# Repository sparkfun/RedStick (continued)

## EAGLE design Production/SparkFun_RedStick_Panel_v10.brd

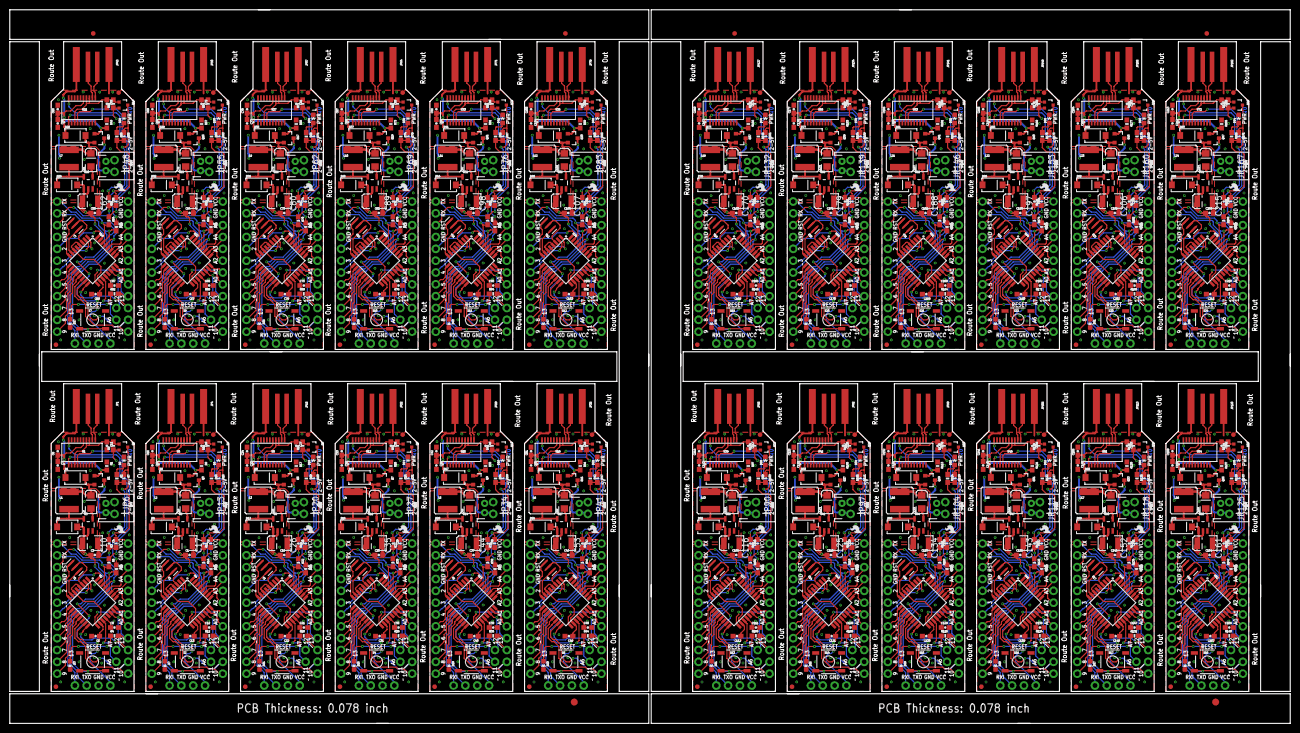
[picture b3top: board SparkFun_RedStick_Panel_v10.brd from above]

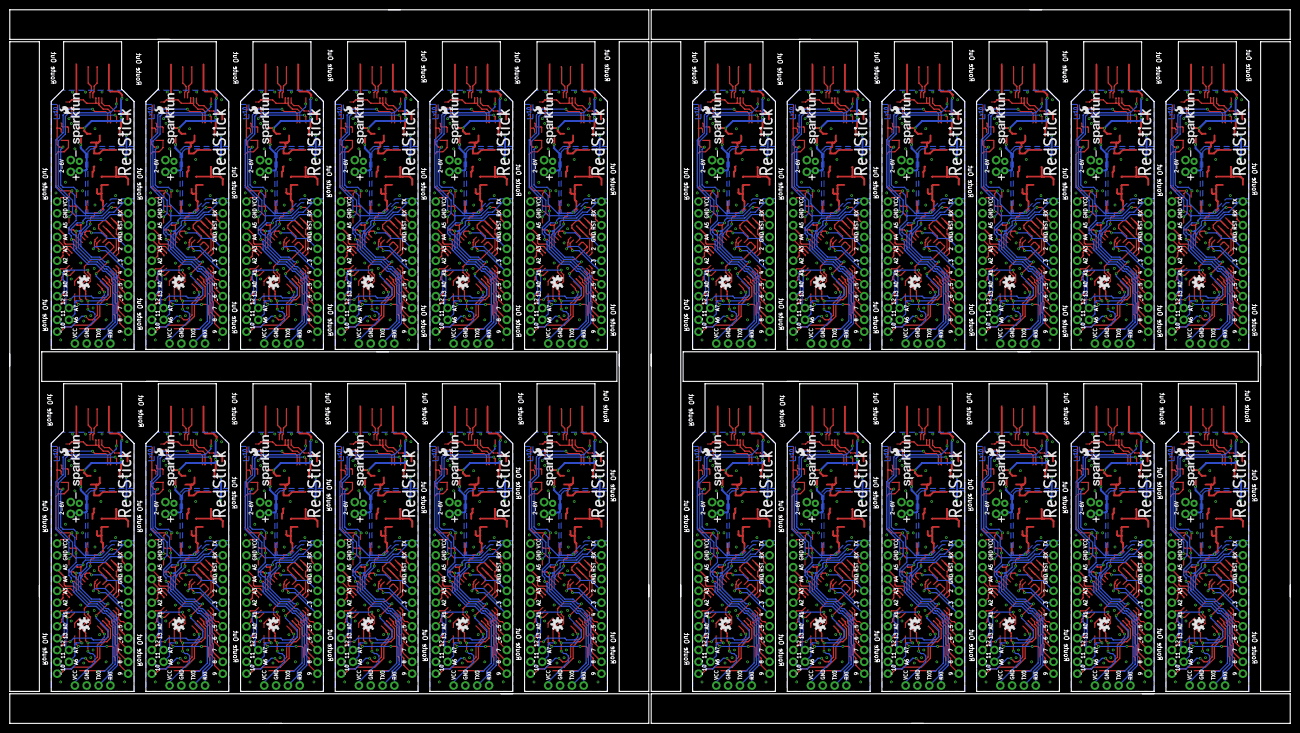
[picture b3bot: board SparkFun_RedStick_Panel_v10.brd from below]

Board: 2 copper layers, 274.8 x 153.2 mm, 990 parts (48 on the bottom side), 984 nets.

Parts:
C1, C2, C3, C4, C5, C6, C7, C8, C11, C12, C13, C14, C15, C18, C19, C20, C21, C22, C23, C24, C27, C28, C29, C30, C31, C32, C33, C36, C37, C38, C39, C40, C41, C42, C45, C46, C47, C48, C49, C50, C51, C54, C55, C56, C57, C58, C59, C60, C63, C64, C65, C66, C67, C68, C69, C72, C73, C74, C75, C76, C77, C78, C81, C82, C83, C84, C85, C86, C87, C90, C91, C92, C93, C94, C95, C96, C99, C100, C101, C102, C103, C104, C105, C108, C109, C110, C111, C112, C113, C114, C117, C118, C119, C120, C121, C122, C123, C126, C127, C128, C129, C130, C131, C132, C135, C136, C137, C138, C139, C140, C141, C144, C145, C146, C147, C148, C149, C150, C153, C154, C155, C156, C157, C158, C159, C162, C163, C164, C165, C166, C167, C168, C171, C172, C173, C174, C175, C176, C177, C180, C181, C182, C183, C184, C185, C186, C189, C190, C191, C192, C193, C194, C195, C198, C199, C200, C201, C202, C203, C204, C207, C208, C209, C210, C211, C212, C213, C216: 0.1uF; 0603-CAP
C9, C16, C25, C34, C43, C52, C61, C70, C79, C88, C97, C106, C115, C124, C133, C142, C151, C160, C169, C178, C187, C196, C205, C214: 10uF; EIA3216
C10, C17, C26, C35, C44, C53, C62, C71, C80, C89, C98, C107, C116, C125, C134, C143, C152, C161, C170, C179, C188, C197, C206, C215: 68uF; EIA3528
D1, D4, D5, D8, D9, D12, D13, D16, D17, D20, D21, D24, D25, D28, D29, D32, D33, D36, D37, D40, D41, D44, D45, D48, D49, D52, D53, D56, D57, D60, D61, D64, D65, D68, D69, D72, D73, D76, D77, D80, D81, D84, D85, D88, D89, D92, D93, D96: MBRA140; SMA-DIODE
D2, D6, D10, D14, D18, D22, D26, D30, D34, D38, D42, D46, D50, D54, D58, D62, D66, D70, D74, D78, D82, D86, D90, D94: RED; LED-0603
D3, D7, D11, D15, D19, D23, D27, D31, D35, D39, D43, D47, D51, D55, D59, D63, D67, D71, D75, D79, D83, D87, D91, D95: GREEN; LED-0603
E$1, E$4: FIDUCIAL-1.5X3
E$2, E$3, E$5, E$6: FIDUCIAL-1X2
FID1, FID2, FID3, FID4, FID5, FID6, FID7, FID8, FID9, FID10, FID11, FID12, FID13, FID14, FID15, FID16, FID17, FID18, FID19, FID20, FID21, FID22, FID23, FID24, FID25, FID26, FID27, FID28, FID29, FID30, FID31, FID32, FID33, FID34, FID35, FID36, FID37, FID38, FID39, FID40, FID41, FID42, FID43, FID44, FID45, FID46, FID47, FID48: FIDUCIAL1X2; FIDUCIAL-1X2
JP1, JP4, JP15, JP22, JP29, JP36, JP43, JP50, JP57, JP64, JP71, JP78, JP85, JP92, JP99, JP106, JP113, JP120, JP127, JP134, JP141, JP148, JP155, JP162: USBPCB_NOPASTE; USB-A-PCB-NOPASTE
JP2, JP3, JP10, JP11, JP17, JP18, JP24, JP25, JP31, JP32, JP38, JP39, JP45, JP46, JP52, JP53, JP59, JP60, JP66, JP67, JP73, JP74, JP80, JP81, JP87, JP88, JP94, JP95, JP101, JP102, JP108, JP109, JP115, JP116, JP122, JP123, JP129, JP130, JP136, JP137, JP143, JP144, JP150, JP151, JP157, JP158, JP164, JP165: DNP; 1X12_NO_SILK
JP5, JP6, JP9, JP13, JP16, JP20, JP23, JP27, JP30, JP34, JP37, JP41, JP44, JP48, JP51, JP55, JP58, JP62, JP65, JP69, JP72, JP76, JP79, JP83, JP86, JP90, JP93, JP97, JP100, JP104, JP107, JP111, JP114, JP118, JP121, JP125, JP128, JP132, JP135, JP139, JP142, JP146, JP149, JP153, JP156, JP160, JP163, JP167: M021X02_NO_SILK; 1X02_NO_SILK
JP7, JP12, JP19, JP26, JP33, JP40, JP47, JP54, JP61, JP68, JP75, JP82, JP89, JP96, JP103, JP110, JP117, JP124, JP131, JP138, JP145, JP152, JP159, JP166: DNP; JST-2-PTH
JP8, JP14, JP21, JP28, JP35, JP42, JP49, JP56, JP63, JP70, JP77, JP84, JP91, JP98, JP105, JP112, JP119, JP126, JP133, JP140, JP147, JP154, JP161, JP168: DNP; 1X04_NO_SILK_ALL_ROUND
L1, L2, L3, L4, L5, L6, L7, L8, L9, L10, L11, L12, L13, L14, L15, L16, L17, L18, L19, L20, L21, L22, L23, L24: 47uH; CR54
LOGO1, LOGO3, LOGO5, LOGO7, LOGO9, LOGO11, LOGO13, LOGO15, LOGO17, LOGO19, LOGO21, LOGO23, LOGO25, LOGO27, LOGO29, LOGO31, LOGO33, LOGO35, LOGO37, LOGO39, LOGO41, LOGO43, LOGO45, LOGO47: SFE_LOGO_FLAME.1_INCH; SFE_LOGO_FLAME_.1
LOGO2, LOGO4, LOGO6, LOGO8, LOGO10, LOGO12, LOGO14, LOGO16, LOGO18, LOGO20, LOGO22, LOGO24, LOGO26, LOGO28, LOGO30, LOGO32, LOGO34, LOGO36, LOGO38, LOGO40, LOGO42, LOGO44, LOGO46, LOGO48: OSHW-LOGOS; OSHW-LOGO-S
Q1, Q3, Q5, Q7, Q9, Q11, Q13, Q15, Q17, Q19, Q21, Q23, Q25, Q27, Q29, Q31, Q33, Q35, Q37, Q39, Q41, Q43, Q45, Q47: DMG2307L; SOT23-3
Q2, Q4, Q6, Q8, Q10, Q12, Q14, Q16, Q18, Q20, Q22, Q24, Q26, Q28, Q30, Q32, Q34, Q36, Q38, Q40, Q42, Q44, Q46, Q48: MOSFET-NCHANNEL2N7002PW; SOT323
R1, R9, R17, R25, R33, R41, R49, R57, R65, R73, R81, R89, R97, R105, R113, R121, R129, R137, R145, R153, R161, R169, R177, R185: 100k; 0603-RES
R2, R10, R18, R26, R34, R42, R50, R58, R66, R74, R82, R90, R98, R106, R114, R122, R130, R138, R146, R154, R162, R170, R178, R186: 6.8K; 0603-RES
R3, R7, R8, R11, R15, R16, R19, R23, R24, R27, R31, R32, R35, R39, R40, R43, R47, R48, R51, R55, R56, R59, R63, R64, R67, R71, R72, R75, R79, R80, R83, R87, R88, R91, R95, R96, R99, R103, R104, R107, R111, R112, R115, R119, R120, R123, R127, R128, R131, R135, R136, R139, R143, R144, R147, R151, R152, R155, R159, R160, R163, R167, R168, R171, R175, R176, R179, R183, R184, R187, R191, R192: 10K; 0603-RES
R4, R12, R20, R28, R36, R44, R52, R60, R68, R76, R84, R92, R100, R108, R116, R124, R132, R140, R148, R156, R164, R172, R180, R188: 2.2k; 0603-RES
R5, R6, R13, R14, R21, R22, R29, R30, R37, R38, R45, R46, R53, R54, R61, R62, R69, R70, R77, R78, R85, R86, R93, R94, R101, R102, R109, R110, R117, R118, R125, R126, R133, R134, R141, R142, R149, R150, R157, R158, R165, R166, R173, R174, R181, R182, R189, R190: 1K; 0603-RES
S1, S2, S3, S4, S5, S6, S7, S8, S9, S10, S11, S12, S13, S14, S15, S16, S17, S18, S19, S20, S21, S22, S23, S24: SWITCH-MOMENTARY-2SMD-REDUNDANT; TACTILE-SWITCH-SMD
U1, U6, U9, U12, U15, U18, U21, U24, U27, U30, U33, U36, U39, U42, U45, U48, U51, U54, U57, U60, U63, U66, U69, U72: FTS31XS-U; SSOP20_L
U2, U4, U7, U10, U13, U16, U19, U22, U25, U28, U31, U34, U37, U40, U43, U46, U49, U52, U55, U58, U61, U64, U67, U70: ATMEGA328P_TQFP; TQFP32-08
U3, U5, U8, U11, U14, U17, U20, U23, U26, U29, U32, U35, U38, U41, U44, U47, U50, U53, U56, U59, U62, U65, U68, U71: 5.0v; SOT23-5
U$1, U$2, U$3, U$4, U$5, U$6, U$7, U$8, U$9, U$10, U$11, U$12, U$13, U$14, U$15, U$16, U$17, U$18, U$19, U$20, U$21, U$22, U$23, U$24: SFE_LOGO_NAME_FLAME.1_INCH; SFE_LOGO_NAME_FLAME_.1
Y1, Y2, Y3, Y4, Y5, Y6, Y7, Y8, Y9, Y10, Y11, Y12, Y13, Y14, Y15, Y16, Y17, Y18, Y19, Y20, Y21, Y22, Y23, Y24: 16MHZ; RESONATOR-SMD

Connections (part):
3.3V: C11.1, Q2.1, R8.2, U1.3, U1.13, U1.14
3.3V1: C18.1, Q4.1, R16.2, U6.3, U6.13, U6.14
3.3V2: C27.1, Q6.1, R24.2, U9.3, U9.13, U9.14
3.3V3: C36.1, Q8.1, R32.2, U12.3, U12.13, U12.14
3.3V4: C45.1, Q10.1, R40.2, U15.3, U15.13, U15.14
3.3V5: C54.1, Q12.1, R48.2, U18.3, U18.13, U18.14
3.3V6: C63.1, Q14.1, R56.2, U21.3, U21.13, U21.14
3.3V7: C72.1, Q16.1, R64.2, U24.3, U24.13, U24.14
3.3V8: C81.1, Q18.1, R72.2, U27.3, U27.13, U27.14
3.3V9: C90.1, Q20.1, R80.2, U30.3, U30.13, U30.14
3.3V10: C99.1, Q22.1, R88.2, U33.3, U33.13, U33.14
3.3V11: C108.1, Q24.1, R96.2, U36.3, U36.13, U36.14
3.3V12: C117.1, Q26.1, R104.2, U39.3, U39.13, U39.14
3.3V13: C126.1, Q28.1, R112.2, U42.3, U42.13, U42.14
3.3V14: C135.1, Q30.1, R120.2, U45.3, U45.13, U45.14
3.3V15: C144.1, Q32.1, R128.2, U48.3, U48.13, U48.14
3.3V16: C153.1, Q34.1, R136.2, U51.3, U51.13, U51.14
3.3V17: C162.1, Q36.1, R144.2, U54.3, U54.13, U54.14
3.3V18: C171.1, Q38.1, R152.2, U57.3, U57.13, U57.14
3.3V19: C180.1, Q40.1, R160.2, U60.3, U60.13, U60.14
3.3V20: C189.1, Q42.1, R168.2, U63.3, U63.13, U63.14
3.3V21: C198.1, Q44.1, R176.2, U66.3, U66.13, U66.14
3.3V22: C207.1, Q46.1, R184.2, U69.3, U69.13, U69.14
3.3V23: C216.1, Q48.1, R192.2, U72.3, U72.13, U72.14
A0: JP3.8, U2.23
A1: JP3.7, U2.24
A2: JP3.6, U2.25
A3: JP3.5, U2.26
A4: JP3.4, U2.27
A5: JP3.3, U2.28
A6: JP5.1, U2.19
A7: JP5.2, U2.22
A8: JP10.8, U4.23
A9: JP10.7, U4.24
A10: JP10.6, U4.25
A11: JP10.5, U4.26
A12: JP10.4, U4.27
A13: JP10.3, U4.28
A14: JP9.1, U4.19
A15: JP9.2, U4.22
A16: JP17.8, U7.23
A17: JP17.7, U7.24
A18: JP17.6, U7.25
A19: JP17.5, U7.26
A20: JP17.4, U7.27
A21: JP17.3, U7.28
A22: JP16.1, U7.19
A23: JP16.2, U7.22
A24: JP24.8, U10.23
A25: JP24.7, U10.24
A26: JP24.6, U10.25
A27: JP24.5, U10.26
A28: JP24.4, U10.27
A29: JP24.3, U10.28
A30: JP23.1, U10.19
A31: JP23.2, U10.22
A32: JP31.8, U13.23
A33: JP31.7, U13.24
A34: JP31.6, U13.25
A35: JP31.5, U13.26
A36: JP31.4, U13.27
A37: JP31.3, U13.28
A38: JP30.1, U13.19
A39: JP30.2, U13.22
A40: JP38.8, U16.23
A41: JP38.7, U16.24
A42: JP38.6, U16.25
A43: JP38.5, U16.26
A44: JP38.4, U16.27
A45: JP38.3, U16.28
A46: JP37.1, U16.19
A47: JP37.2, U16.22
A48: JP45.8, U19.23
A49: JP45.7, U19.24
A50: JP45.6, U19.25
A51: JP45.5, U19.26
A52: JP45.4, U19.27
A53: JP45.3, U19.28
A54: JP44.1, U19.19
A55: JP44.2, U19.22
A56: JP52.8, U22.23
A57: JP52.7, U22.24
A58: JP52.6, U22.25
A59: JP52.5, U22.26
A60: JP52.4, U22.27
A61: JP52.3, U22.28
A62: JP51.1, U22.19
A63: JP51.2, U22.22
A64: JP59.8, U25.23
A65: JP59.7, U25.24
A66: JP59.6, U25.25
A67: JP59.5, U25.26
A68: JP59.4, U25.27
A69: JP59.3, U25.28
A70: JP58.1, U25.19
A71: JP58.2, U25.22
A72: JP66.8, U28.23
A73: JP66.7, U28.24
A74: JP66.6, U28.25
A75: JP66.5, U28.26
A76: JP66.4, U28.27
A77: JP66.3, U28.28
A78: JP65.1, U28.19
A79: JP65.2, U28.22
A80: JP73.8, U31.23
A81: JP73.7, U31.24
A82: JP73.6, U31.25
A83: JP73.5, U31.26
A84: JP73.4, U31.27
A85: JP73.3, U31.28
A86: JP72.1, U31.19
A87: JP72.2, U31.22
A88: JP80.8, U34.23
A89: JP80.7, U34.24
A90: JP80.6, U34.25
A91: JP80.5, U34.26
A92: JP80.4, U34.27
A93: JP80.3, U34.28
A94: JP79.1, U34.19
A95: JP79.2, U34.22
A96: JP87.8, U37.23
A97: JP87.7, U37.24
A98: JP87.6, U37.25
A99: JP87.5, U37.26
A100: JP87.4, U37.27
A101: JP87.3, U37.28
A102: JP86.1, U37.19
A103: JP86.2, U37.22
A104: JP94.8, U40.23
A105: JP94.7, U40.24
A106: JP94.6, U40.25
A107: JP94.5, U40.26
A108: JP94.4, U40.27
A109: JP94.3, U40.28
A110: JP93.1, U40.19
A111: JP93.2, U40.22
A112: JP101.8, U43.23
A113: JP101.7, U43.24
A114: JP101.6, U43.25
A115: JP101.5, U43.26
A116: JP101.4, U43.27
A117: JP101.3, U43.28
A118: JP100.1, U43.19
A119: JP100.2, U43.22
A120: JP108.8, U46.23
A121: JP108.7, U46.24
A122: JP108.6, U46.25
A123: JP108.5, U46.26
A124: JP108.4, U46.27
A125: JP108.3, U46.28
A126: JP107.1, U46.19
A127: JP107.2, U46.22
A128: JP115.8, U49.23
A129: JP115.7, U49.24
A130: JP115.6, U49.25
A131: JP115.5, U49.26
A132: JP115.4, U49.27
A133: JP115.3, U49.28
A134: JP114.1, U49.19
A135: JP114.2, U49.22
A136: JP122.8, U52.23
A137: JP122.7, U52.24
A138: JP122.6, U52.25
A139: JP122.5, U52.26
A140: JP122.4, U52.27
A141: JP122.3, U52.28
A142: JP121.1, U52.19
A143: JP121.2, U52.22
A144: JP129.8, U55.23
A145: JP129.7, U55.24
A146: JP129.6, U55.25
A147: JP129.5, U55.26
A148: JP129.4, U55.27
A149: JP129.3, U55.28
A150: JP128.1, U55.19
A151: JP128.2, U55.22
A152: JP136.8, U58.23
A153: JP136.7, U58.24
A154: JP136.6, U58.25
A155: JP136.5, U58.26
A156: JP136.4, U58.27
A157: JP136.3, U58.28
A158: JP135.1, U58.19
A159: JP135.2, U58.22
A160: JP143.8, U61.23
A161: JP143.7, U61.24
A162: JP143.6, U61.25
A163: JP143.5, U61.26
A164: JP143.4, U61.27
A165: JP143.3, U61.28
A166: JP142.1, U61.19
A167: JP142.2, U61.22
A168: JP150.8, U64.23
A169: JP150.7, U64.24
A170: JP150.6, U64.25
A171: JP150.5, U64.26
A172: JP150.4, U64.27
A173: JP150.3, U64.28
A174: JP149.1, U64.19
A175: JP149.2, U64.22
A176: JP157.8, U67.23
A177: JP157.7, U67.24
A178: JP157.6, U67.25
A179: JP157.5, U67.26
A180: JP157.4, U67.27
A181: JP157.3, U67.28
A182: JP156.1, U67.19
A183: JP156.2, U67.22
A184: JP164.8, U70.23
A185: JP164.7, U70.24
A186: JP164.6, U70.25
A187: JP164.5, U70.26
A188: JP164.4, U70.27
A189: JP164.3, U70.28
A190: JP163.1, U70.19
A191: JP163.2, U70.22
AREF: C5.1, U2.20
AREF1: C12.1, U4.20
AREF2: C21.1, U7.20
AREF3: C30.1, U10.20
AREF4: C39.1, U13.20
AREF5: C48.1, U16.20
AREF6: C57.1, U19.20
AREF7: C66.1, U22.20
AREF8: C75.1, U25.20
AREF9: C84.1, U28.20
AREF10: C93.1, U31.20
AREF11: C102.1, U34.20
AREF12: C111.1, U37.20
AREF13: C120.1, U40.20
AREF14: C129.1, U43.20
AREF15: C138.1, U46.20
AREF16: C147.1, U49.20
AREF17: C156.1, U52.20
AREF18: C165.1, U55.20
AREF19: C174.1, U58.20
AREF20: C183.1, U61.20
AREF21: C192.1, U64.20
AREF22: C201.1, U67.20
AREF23: C210.1, U70.20
D1: JP11.8, U4.32
D2: JP2.8, U2.32
D3: JP2.7, U2.1
D4: JP2.6, U2.2
D5: JP2.5, U2.9
D6: JP2.4, U2.10
D7: JP2.3, U2.11
D8: JP2.2, U2.12
D9: JP2.1, U2.13
D10: JP3.12, U2.14
D11: JP11.7, U4.1
D12: JP11.6, U4.2
D13: JP11.5, U4.9
D14: JP11.4, U4.10
D15: JP11.3, U4.11
D16: JP11.2, U4.12
D17: JP11.1, U4.13
D18: JP10.12, U4.14
D19: JP18.8, U7.32
D20: JP18.7, U7.1
D21: JP18.6, U7.2
D22: JP18.5, U7.9
D23: JP18.4, U7.10
D24: JP18.3, U7.11
D25: JP18.2, U7.12
D26: JP18.1, U7.13
D27: JP17.12, U7.14
D28: JP25.8, U10.32
D29: JP25.7, U10.1
D30: JP25.6, U10.2
D31: JP25.5, U10.9
D32: JP25.4, U10.10
D33: JP25.3, U10.11
D34: JP25.2, U10.12
D35: JP25.1, U10.13
D36: JP24.12, U10.14
D37: JP32.8, U13.32
D38: JP32.7, U13.1
D39: JP32.6, U13.2
D40: JP32.5, U13.9
D41: JP32.4, U13.10
D42: JP32.3, U13.11
D43: JP32.2, U13.12
D44: JP32.1, U13.13
D45: JP31.12, U13.14
D46: JP39.8, U16.32
D47: JP39.7, U16.1
D48: JP39.6, U16.2
D49: JP39.5, U16.9
D50: JP39.4, U16.10
D51: JP39.3, U16.11
D52: JP39.2, U16.12
D53: JP39.1, U16.13
D54: JP38.12, U16.14
D55: JP46.8, U19.32
D56: JP46.7, U19.1
D57: JP46.6, U19.2
D58: JP46.5, U19.9
D59: JP46.4, U19.10
D60: JP46.3, U19.11
D61: JP46.2, U19.12
D62: JP46.1, U19.13
D63: JP45.12, U19.14
D64: JP53.8, U22.32
D65: JP53.7, U22.1
D66: JP53.6, U22.2
D67: JP53.5, U22.9
D68: JP53.4, U22.10
D69: JP53.3, U22.11
D70: JP53.2, U22.12
D71: JP53.1, U22.13
D72: JP52.12, U22.14
D73: JP60.8, U25.32
D74: JP60.7, U25.1
D75: JP60.6, U25.2
D76: JP60.5, U25.9
D77: JP60.4, U25.10
D78: JP60.3, U25.11
D79: JP60.2, U25.12
D80: JP60.1, U25.13
D81: JP59.12, U25.14
D82: JP67.8, U28.32
D83: JP67.7, U28.1
D84: JP67.6, U28.2
D85: JP67.5, U28.9
D86: JP67.4, U28.10
D87: JP67.3, U28.11
D88: JP67.2, U28.12
D89: JP67.1, U28.13
D90: JP66.12, U28.14
D91: JP74.8, U31.32
D92: JP74.7, U31.1
D93: JP74.6, U31.2
D94: JP74.5, U31.9
D95: JP74.4, U31.10
D96: JP74.3, U31.11
D97: JP74.2, U31.12
D98: JP74.1, U31.13
D99: JP73.12, U31.14
D100: JP81.8, U34.32
D101: JP81.7, U34.1
D102: JP81.6, U34.2
D103: JP81.5, U34.9
D104: JP81.4, U34.10
D105: JP81.3, U34.11
D106: JP81.2, U34.12
D107: JP81.1, U34.13
D108: JP80.12, U34.14
D109: JP88.8, U37.32
D110: JP88.7, U37.1
D111: JP88.6, U37.2
D112: JP88.5, U37.9
D113: JP88.4, U37.10
D114: JP88.3, U37.11
D115: JP88.2, U37.12
D116: JP88.1, U37.13
D117: JP87.12, U37.14
D118: JP95.8, U40.32
D119: JP95.7, U40.1
D120: JP95.6, U40.2
D121: JP95.5, U40.9
D122: JP95.4, U40.10
D123: JP95.3, U40.11
D124: JP95.2, U40.12
D125: JP95.1, U40.13
D126: JP94.12, U40.14
D127: JP102.8, U43.32
D128: JP102.7, U43.1
D129: JP102.6, U43.2
D130: JP102.5, U43.9
D131: JP102.4, U43.10
D132: JP102.3, U43.11
D133: JP102.2, U43.12
D134: JP102.1, U43.13
D135: JP101.12, U43.14
D136: JP109.8, U46.32
D137: JP109.7, U46.1
D138: JP109.6, U46.2
D139: JP109.5, U46.9
D140: JP109.4, U46.10
D141: JP109.3, U46.11
D142: JP109.2, U46.12
D143: JP109.1, U46.13
D144: JP108.12, U46.14
D145: JP116.8, U49.32
D146: JP116.7, U49.1
D147: JP116.6, U49.2
D148: JP116.5, U49.9
D149: JP116.4, U49.10
D150: JP116.3, U49.11
D151: JP116.2, U49.12
D152: JP116.1, U49.13
D153: JP115.12, U49.14
D154: JP123.8, U52.32
D155: JP123.7, U52.1
D156: JP123.6, U52.2
D157: JP123.5, U52.9
D158: JP123.4, U52.10
D159: JP123.3, U52.11
D160: JP123.2, U52.12
D161: JP123.1, U52.13
D162: JP122.12, U52.14
D163: JP130.8, U55.32
D164: JP130.7, U55.1
D165: JP130.6, U55.2
D166: JP130.5, U55.9
D167: JP130.4, U55.10
D168: JP130.3, U55.11
D169: JP130.2, U55.12
D170: JP130.1, U55.13
D171: JP129.12, U55.14
D172: JP137.8, U58.32
D173: JP137.7, U58.1
D174: JP137.6, U58.2
D175: JP137.5, U58.9
D176: JP137.4, U58.10
D177: JP137.3, U58.11
D178: JP137.2, U58.12
D179: JP137.1, U58.13
D180: JP136.12, U58.14
D181: JP144.8, U61.32
D182: JP144.7, U61.1
D183: JP144.6, U61.2
D184: JP144.5, U61.9
D185: JP144.4, U61.10
D186: JP144.3, U61.11
D187: JP144.2, U61.12
D188: JP144.1, U61.13
D189: JP143.12, U61.14
D190: JP151.8, U64.32
D191: JP151.7, U64.1
D192: JP151.6, U64.2
D193: JP151.5, U64.9
D194: JP151.4, U64.10
D195: JP151.3, U64.11
D196: JP151.2, U64.12
D197: JP151.1, U64.13
D198: JP150.12, U64.14
D199: JP158.8, U67.32
D200: JP158.7, U67.1
D201: JP158.6, U67.2
D202: JP158.5, U67.9
D203: JP158.4, U67.10
D204: JP158.3, U67.11
D205: JP158.2, U67.12
D206: JP158.1, U67.13
D207: JP157.12, U67.14
D208: JP165.8, U70.32
D209: JP165.7, U70.1
D210: JP165.6, U70.2
D211: JP165.5, U70.9
D212: JP165.4, U70.10
D213: JP165.3, U70.11
D214: JP165.2, U70.12
D215: JP165.1, U70.13
D216: JP164.12, U70.14
D+: JP1.USB_P, U1.11
D+1: JP4.USB_P, U6.11
D+2: JP15.USB_P, U9.11
D+3: JP22.USB_P, U12.11
D+4: JP29.USB_P, U15.11
D+5: JP36.USB_P, U18.11
D+6: JP43.USB_P, U21.11
D+7: JP50.USB_P, U24.11
D+8: JP57.USB_P, U27.11
D+9: JP64.USB_P, U30.11
D+10: JP71.USB_P, U33.11
D+11: JP78.USB_P, U36.11
D+12: JP85.USB_P, U39.11
D+13: JP92.USB_P, U42.11
D+14: JP99.USB_P, U45.11
D+15: JP106.USB_P, U48.11
D+16: JP113.USB_P, U51.11
D+17: JP120.USB_P, U54.11
D+18: JP127.USB_P, U57.11
D+19: JP134.USB_P, U60.11
D+20: JP141.USB_P, U63.11
D+21: JP148.USB_P, U66.11
D+22: JP155.USB_P, U69.11
D+23: JP162.USB_P, U72.11
D-: JP1.USB_M, U1.12
D-1: JP4.USB_M, U6.12
D-2: JP15.USB_M, U9.12
D-3: JP22.USB_M, U12.12
D-4: JP29.USB_M, U15.12
D-5: JP36.USB_M, U18.12
D-6: JP43.USB_M, U21.12
D-7: JP50.USB_M, U24.12
D-8: JP57.USB_M, U27.12
D-9: JP64.USB_M, U30.12
D-10: JP71.USB_M, U33.12
D-11: JP78.USB_M, U36.12
D-12: JP85.USB_M, U39.12
D-13: JP92.USB_M, U42.12
D-14: JP99.USB_M, U45.12
D-15: JP106.USB_M, U48.12
D-16: JP113.USB_M, U51.12
D-17: JP120.USB_M, U54.12
D-18: JP127.USB_M, U57.12
D-19: JP134.USB_M, U60.12
D-20: JP141.USB_M, U63.12
D-21: JP148.USB_M, U66.12
D-22: JP155.USB_M, U69.12
D-23: JP162.USB_M, U72.12
DTR: C4.1, Q2.3, R7.1
DTR1: C2.1, Q4.3, R15.1
DTR2: C20.1, Q6.3, R23.1
DTR3: C29.1, Q8.3, R31.1
DTR4: C38.1, Q10.3, R39.1
DTR5: C47.1, Q12.3, R47.1
DTR6: C56.1, Q14.3, R55.1
DTR7: C65.1, Q16.3, R63.1
DTR8: C74.1, Q18.3, R71.1
DTR9: C83.1, Q20.3, R79.1
DTR10: C92.1, Q22.3, R87.1
DTR11: C101.1, Q24.3, R95.1
DTR12: C110.1, Q26.3, R103.1
DTR13: C119.1, Q28.3, R111.1
DTR14: C128.1, Q30.3, R119.1
DTR15: C137.1, Q32.3, R127.1
DTR16: C146.1, Q34.3, R135.1
DTR17: C155.1, Q36.3, R143.1
DTR18: C164.1, Q38.3, R151.1
DTR19: C173.1, Q40.3, R159.1
DTR20: C182.1, Q42.3, R167.1
DTR21: C191.1, Q44.3, R175.1
DTR22: C200.1, Q46.3, R183.1
DTR23: C209.1, Q48.3, R191.1
GND: C3.2, C5.2, C6.2, C7.2, C8.2, C9.C, C10.C, C11.2, D2.C, D3.C, JP1.GND, JP2.9, JP3.2, JP6.1, JP7.1, JP8.2, R1.1, S1.1, S1.2, U1.6, U1.16, U2.3, U2.5, U2.21, U3.4, Y1.2
GND1: C1.2, C12.2, C13.2, C14.2, C15.2, C16.C, C17.C, C18.2, D6.C, D7.C, JP4.GND, JP10.2, JP11.9, JP12.1, JP13.1, JP14.2, R9.1, S2.1, S2.2, U4.3, U4.5, U4.21, U5.4, U6.6, U6.16, Y2.2
GND2: C19.2, C21.2, C22.2, C23.2, C24.2, C25.C, C26.C, C27.2, D10.C, D11.C, JP15.GND, JP17.2, JP18.9, JP19.1, JP20.1, JP21.2, R17.1, S3.1, S3.2, U7.3, U7.5, U7.21, U8.4, U9.6, U9.16, Y3.2
GND3: C28.2, C30.2, C31.2, C32.2, C33.2, C34.C, C35.C, C36.2, D14.C, D15.C, JP22.GND, JP24.2, JP25.9, JP26.1, JP27.1, JP28.2, R25.1, S4.1, S4.2, U10.3, U10.5, U10.21, U11.4, U12.6, U12.16, Y4.2
GND4: C37.2, C39.2, C40.2, C41.2, C42.2, C43.C, C44.C, C45.2, D18.C, D19.C, JP29.GND, JP31.2, JP32.9, JP33.1, JP34.1, JP35.2, R33.1, S5.1, S5.2, U13.3, U13.5, U13.21, U14.4, U15.6, U15.16, Y5.2
GND5: C46.2, C48.2, C49.2, C50.2, C51.2, C52.C, C53.C, C54.2, D22.C, D23.C, JP36.GND, JP38.2, JP39.9, JP40.1, JP41.1, JP42.2, R41.1, S6.1, S6.2, U16.3, U16.5, U16.21, U17.4, U18.6, U18.16, Y6.2
GND6: C55.2, C57.2, C58.2, C59.2, C60.2, C61.C, C62.C, C63.2, D26.C, D27.C, JP43.GND, JP45.2, JP46.9, JP47.1, JP48.1, JP49.2, R49.1, S7.1, S7.2, U19.3, U19.5, U19.21, U20.4, U21.6, U21.16, Y7.2
GND7: C64.2, C66.2, C67.2, C68.2, C69.2, C70.C, C71.C, C72.2, D30.C, D31.C, JP50.GND, JP52.2, JP53.9, JP54.1, JP55.1, JP56.2, R57.1, S8.1, S8.2, U22.3, U22.5, U22.21, U23.4, U24.6, U24.16, Y8.2
GND8: C73.2, C75.2, C76.2, C77.2, C78.2, C79.C, C80.C, C81.2, D34.C, D35.C, JP57.GND, JP59.2, JP60.9, JP61.1, JP62.1, JP63.2, R65.1, S9.1, S9.2, U25.3, U25.5, U25.21, U26.4, U27.6, U27.16, Y9.2
GND9: C82.2, C84.2, C85.2, C86.2, C87.2, C88.C, C89.C, C90.2, D38.C, D39.C, JP64.GND, JP66.2, JP67.9, JP68.1, JP69.1, JP70.2, R73.1, S10.1, S10.2, U28.3, U28.5, U28.21, U29.4, U30.6, U30.16, Y10.2
GND10: C91.2, C93.2, C94.2, C95.2, C96.2, C97.C, C98.C, C99.2, D42.C, D43.C, JP71.GND, JP73.2, JP74.9, JP75.1, JP76.1, JP77.2, R81.1, S11.1, S11.2, U31.3, U31.5, U31.21, U32.4, U33.6, U33.16, Y11.2
GND11: C100.2, C102.2, C103.2, C104.2, C105.2, C106.C, C107.C, C108.2, D46.C, D47.C, JP78.GND, JP80.2, JP81.9, JP82.1, JP83.1, JP84.2, R89.1, S12.1, S12.2, U34.3, U34.5, U34.21, U35.4, U36.6, U36.16, Y12.2
GND12: C109.2, C111.2, C112.2, C113.2, C114.2, C115.C, C116.C, C117.2, D50.C, D51.C, JP85.GND, JP87.2, JP88.9, JP89.1, JP90.1, JP91.2, R97.1, S13.1, S13.2, U37.3, U37.5, U37.21, U38.4, U39.6, U39.16, Y13.2
GND13: C118.2, C120.2, C121.2, C122.2, C123.2, C124.C, C125.C, C126.2, D54.C, D55.C, JP92.GND, JP94.2, JP95.9, JP96.1, JP97.1, JP98.2, R105.1, S14.1, S14.2, U40.3, U40.5, U40.21, U41.4, U42.6, U42.16, Y14.2
GND14: C127.2, C129.2, C130.2, C131.2, C132.2, C133.C, C134.C, C135.2, D58.C, D59.C, JP99.GND, JP101.2, JP102.9, JP103.1, JP104.1, JP105.2, R113.1, S15.1, S15.2, U43.3, U43.5, U43.21, U44.4, U45.6, U45.16, Y15.2
GND15: C136.2, C138.2, C139.2, C140.2, C141.2, C142.C, C143.C, C144.2, D62.C, D63.C, JP106.GND, JP108.2, JP109.9, JP110.1, JP111.1, JP112.2, R121.1, S16.1, S16.2, U46.3, U46.5, U46.21, U47.4, U48.6, U48.16, Y16.2
GND16: C145.2, C147.2, C148.2, C149.2, C150.2, C151.C, C152.C, C153.2, D66.C, D67.C, JP113.GND, JP115.2, JP116.9, JP117.1, JP118.1, JP119.2, R129.1, S17.1, S17.2, U49.3, U49.5, U49.21, U50.4, U51.6, U51.16, Y17.2
GND17: C154.2, C156.2, C157.2, C158.2, C159.2, C160.C, C161.C, C162.2, D70.C, D71.C, JP120.GND, JP122.2, JP123.9, JP124.1, JP125.1, JP126.2, R137.1, S18.1, S18.2, U52.3, U52.5, U52.21, U53.4, U54.6, U54.16, Y18.2
GND18: C163.2, C165.2, C166.2, C167.2, C168.2, C169.C, C170.C, C171.2, D74.C, D75.C, JP127.GND, JP129.2, JP130.9, JP131.1, JP132.1, JP133.2, R145.1, S19.1, S19.2, U55.3, U55.5, U55.21, U56.4, U57.6, U57.16, Y19.2
GND19: C172.2, C174.2, C175.2, C176.2, C177.2, C178.C, C179.C, C180.2, D78.C, D79.C, JP134.GND, JP136.2, JP137.9, JP138.1, JP139.1, JP140.2, R153.1, S20.1, S20.2, U58.3, U58.5, U58.21, U59.4, U60.6, U60.16, Y20.2
GND20: C181.2, C183.2, C184.2, C185.2, C186.2, C187.C, C188.C, C189.2, D82.C, D83.C, JP141.GND, JP143.2, JP144.9, JP145.1, JP146.1, JP147.2, R161.1, S21.1, S21.2, U61.3, U61.5, U61.21, U62.4, U63.6, U63.16, Y21.2
GND21: C190.2, C192.2, C193.2, C194.2, C195.2, C196.C, C197.C, C198.2, D86.C, D87.C, JP148.GND, JP150.2, JP151.9, JP152.1, JP153.1, JP154.2, R169.1, S22.1, S22.2, U64.3, U64.5, U64.21, U65.4, U66.6, U66.16, Y22.2
GND22: C199.2, C201.2, C202.2, C203.2, C204.2, C205.C, C206.C, C207.2, D90.C, D91.C, JP155.GND, JP157.2, JP158.9, JP159.1, JP160.1, JP161.2, R177.1, S23.1, S23.2, U67.3, U67.5, U67.21, U68.4, U69.6, U69.16, Y23.2
GND23: C208.2, C210.2, C211.2, C212.2, C213.2, C214.C, C215.C, C216.2, D94.C, D95.C, JP162.GND, JP164.2, JP165.9, JP166.1, JP167.1, JP168.2, R185.1, S24.1, S24.2, U70.3, U70.5, U70.21, U71.4, U72.6, U72.16, Y24.2
MISO: JP3.10, U2.16
MISO1: JP10.10, U4.16
MISO2: JP17.10, U7.16
MISO3: JP24.10, U10.16
MISO4: JP31.10, U13.16
MISO5: JP38.10, U16.16
MISO6: JP45.10, U19.16
MISO7: JP52.10, U22.16
MISO8: JP59.10, U25.16
MISO9: JP66.10, U28.16
MISO10: JP73.10, U31.16
MISO11: JP80.10, U34.16
MISO12: JP87.10, U37.16
MISO13: JP94.10, U40.16
MISO14: JP101.10, U43.16
MISO15: JP108.10, U46.16
MISO16: JP115.10, U49.16
MISO17: JP122.10, U52.16
MISO18: JP129.10, U55.16
MISO19: JP136.10, U58.16
MISO20: JP143.10, U61.16
MISO21: JP150.10, U64.16
MISO22: JP157.10, U67.16
MISO23: JP164.10, U70.16
MOSI: JP3.11, U2.15
MOSI1: JP10.11, U4.15
MOSI2: JP17.11, U7.15
MOSI3: JP24.11, U10.15
MOSI4: JP31.11, U13.15
MOSI5: JP38.11, U16.15
MOSI6: JP45.11, U19.15
MOSI7: JP52.11, U22.15
MOSI8: JP59.11, U25.15
MOSI9: JP66.11, U28.15
MOSI10: JP73.11, U31.15
MOSI11: JP80.11, U34.15
MOSI12: JP87.11, U37.15
MOSI13: JP94.11, U40.15
MOSI14: JP101.11, U43.15
MOSI15: JP108.11, U46.15
MOSI16: JP115.11, U49.15
MOSI17: JP122.11, U52.15
MOSI18: JP129.11, U55.15
MOSI19: JP136.11, U58.15
MOSI20: JP143.11, U61.15
MOSI21: JP150.11, U64.15
MOSI22: JP157.11, U67.15
MOSI23: JP164.11, U70.15
unnamed: D3.A, R4.1
unnamed: D7.A, R12.1
unnamed: R5.1, U1.20
unnamed: D2.A, R2.1
unnamed: U2.7, Y1.1
unnamed: U2.8, Y1.3
unnamed: R6.1, U1.4
unnamed: D4.A, L1.P$2, U3.5
unnamed: Q2.2, R8.1, U1.1
unnamed: U4.7, Y2.1
unnamed: U4.8, Y2.3
unnamed: R13.1, U6.20
unnamed: R14.1, U6.4
unnamed: D8.A, L2.P$2, U5.5
unnamed: D6.A, R10.1
unnamed: Q4.2, R16.1, U6.1
unnamed: D11.A, R20.1
unnamed: U7.7, Y3.1
unnamed: U7.8, Y3.3
unnamed: R21.1, U9.20
unnamed: R22.1, U9.4
unnamed: D12.A, L3.P$2, U8.5
unnamed: D10.A, R18.1
unnamed: Q6.2, R24.1, U9.1
unnamed: D15.A, R28.1
unnamed: U10.7, Y4.1
unnamed: U10.8, Y4.3
unnamed: R29.1, U12.20
unnamed: R30.1, U12.4
unnamed: D16.A, L4.P$2, U11.5
unnamed: D14.A, R26.1
unnamed: Q8.2, R32.1, U12.1
unnamed: D19.A, R36.1
unnamed: U13.7, Y5.1
unnamed: U13.8, Y5.3
unnamed: R37.1, U15.20
unnamed: R38.1, U15.4
unnamed: D20.A, L5.P$2, U14.5
unnamed: D18.A, R34.1
unnamed: Q10.2, R40.1, U15.1
unnamed: D23.A, R44.1
unnamed: U16.7, Y6.1
unnamed: U16.8, Y6.3
unnamed: R45.1, U18.20
unnamed: R46.1, U18.4
unnamed: D24.A, L6.P$2, U17.5
unnamed: D22.A, R42.1
unnamed: Q12.2, R48.1, U18.1
unnamed: D27.A, R52.1
unnamed: U19.7, Y7.1
unnamed: U19.8, Y7.3
unnamed: R53.1, U21.20
unnamed: R54.1, U21.4
unnamed: D28.A, L7.P$2, U20.5
unnamed: D26.A, R50.1
unnamed: Q14.2, R56.1, U21.1
unnamed: D31.A, R60.1
unnamed: U22.7, Y8.1
unnamed: U22.8, Y8.3
unnamed: R61.1, U24.20
unnamed: R62.1, U24.4
unnamed: D32.A, L8.P$2, U23.5
unnamed: D30.A, R58.1
unnamed: Q16.2, R64.1, U24.1
unnamed: D35.A, R68.1
unnamed: U25.7, Y9.1
unnamed: U25.8, Y9.3
unnamed: R69.1, U27.20
unnamed: R70.1, U27.4
unnamed: D36.A, L9.P$2, U26.5
unnamed: D34.A, R66.1
unnamed: Q18.2, R72.1, U27.1
unnamed: D39.A, R76.1
unnamed: U28.7, Y10.1
unnamed: U28.8, Y10.3
unnamed: R77.1, U30.20
unnamed: R78.1, U30.4
unnamed: D40.A, L10.P$2, U29.5
unnamed: D38.A, R74.1
unnamed: Q20.2, R80.1, U30.1
unnamed: D43.A, R84.1
unnamed: U31.7, Y11.1
unnamed: U31.8, Y11.3
unnamed: R85.1, U33.20
unnamed: R86.1, U33.4
unnamed: D44.A, L11.P$2, U32.5
unnamed: D42.A, R82.1
unnamed: Q22.2, R88.1, U33.1
unnamed: D47.A, R92.1
unnamed: U34.7, Y12.1
unnamed: U34.8, Y12.3
unnamed: R93.1, U36.20
unnamed: R94.1, U36.4
unnamed: D48.A, L12.P$2, U35.5
unnamed: D46.A, R90.1
unnamed: Q24.2, R96.1, U36.1
unnamed: D51.A, R100.1
unnamed: U37.7, Y13.1
unnamed: U37.8, Y13.3
unnamed: R101.1, U39.20
unnamed: R102.1, U39.4
unnamed: D52.A, L13.P$2, U38.5
unnamed: D50.A, R98.1
unnamed: Q26.2, R104.1, U39.1
unnamed: D55.A, R108.1
unnamed: U40.7, Y14.1
unnamed: U40.8, Y14.3
unnamed: R109.1, U42.20
unnamed: R110.1, U42.4
unnamed: D56.A, L14.P$2, U41.5
unnamed: D54.A, R106.1
unnamed: Q28.2, R112.1, U42.1
unnamed: D59.A, R116.1
unnamed: U43.7, Y15.1
unnamed: U43.8, Y15.3
unnamed: R117.1, U45.20
unnamed: R118.1, U45.4
unnamed: D60.A, L15.P$2, U44.5
unnamed: D58.A, R114.1
unnamed: Q30.2, R120.1, U45.1
unnamed: D63.A, R124.1
unnamed: U46.7, Y16.1
unnamed: U46.8, Y16.3
unnamed: R125.1, U48.20
unnamed: R126.1, U48.4
unnamed: D64.A, L16.P$2, U47.5
unnamed: D62.A, R122.1
unnamed: Q32.2, R128.1, U48.1
unnamed: D67.A, R132.1
unnamed: U49.7, Y17.1
unnamed: U49.8, Y17.3
unnamed: R133.1, U51.20
unnamed: R134.1, U51.4
unnamed: D68.A, L17.P$2, U50.5
unnamed: D66.A, R130.1
unnamed: Q34.2, R136.1, U51.1
unnamed: D71.A, R140.1
unnamed: U52.7, Y18.1
unnamed: U52.8, Y18.3
unnamed: R141.1, U54.20
unnamed: R142.1, U54.4
unnamed: D72.A, L18.P$2, U53.5
unnamed: D70.A, R138.1
unnamed: Q36.2, R144.1, U54.1
unnamed: D75.A, R148.1
unnamed: U55.7, Y19.1
unnamed: U55.8, Y19.3
unnamed: R149.1, U57.20
unnamed: R150.1, U57.4
unnamed: D76.A, L19.P$2, U56.5
unnamed: D74.A, R146.1
unnamed: Q38.2, R152.1, U57.1
unnamed: D79.A, R156.1
unnamed: U58.7, Y20.1
unnamed: U58.8, Y20.3
unnamed: R157.1, U60.20
unnamed: R158.1, U60.4
unnamed: D80.A, L20.P$2, U59.5
unnamed: D78.A, R154.1
unnamed: Q40.2, R160.1, U60.1
unnamed: D83.A, R164.1
unnamed: U61.7, Y21.1
unnamed: U61.8, Y21.3
unnamed: R165.1, U63.20
unnamed: R166.1, U63.4
unnamed: D84.A, L21.P$2, U62.5
unnamed: D82.A, R162.1
unnamed: Q42.2, R168.1, U63.1
unnamed: D87.A, R172.1
unnamed: U64.7, Y22.1
unnamed: U64.8, Y22.3
unnamed: R173.1, U66.20
unnamed: R174.1, U66.4
unnamed: D88.A, L22.P$2, U65.5
unnamed: D86.A, R170.1
unnamed: Q44.2, R176.1, U66.1
unnamed: D91.A, R180.1
unnamed: U67.7, Y23.1
unnamed: U67.8, Y23.3
unnamed: R181.1, U69.20
unnamed: R182.1, U69.4
unnamed: D92.A, L23.P$2, U68.5
unnamed: D90.A, R178.1
unnamed: Q46.2, R184.1, U69.1
unnamed: D95.A, R188.1
unnamed: U70.7, Y24.1
unnamed: U70.8, Y24.3
unnamed: R189.1, U72.20
unnamed: R190.1, U72.4
unnamed: D96.A, L24.P$2, U71.5
unnamed: D94.A, R186.1
unnamed: Q48.2, R192.1, U72.1
RESET: C4.2, JP2.10, R3.1, S1.3, S1.4, U2.29
RESET1: C2.2, JP11.10, R11.1, S2.3, S2.4, U4.29
RESET2: C20.2, JP18.10, R19.1, S3.3, S3.4, U7.29
RESET3: C29.2, JP25.10, R27.1, S4.3, S4.4, U10.29
RESET4: C38.2, JP32.10, R35.1, S5.3, S5.4, U13.29
RESET5: C47.2, JP39.10, R43.1, S6.3, S6.4, U16.29
RESET6: C56.2, JP46.10, R51.1, S7.3, S7.4, U19.29
RESET7: C65.2, JP53.10, R59.1, S8.3, S8.4, U22.29
RESET8: C74.2, JP60.10, R67.1, S9.3, S9.4, U25.29
RESET9: C83.2, JP67.10, R75.1, S10.3, S10.4, U28.29
RESET10: C92.2, JP74.10, R83.1, S11.3, S11.4, U31.29
RESET11: C101.2, JP81.10, R91.1, S12.3, S12.4, U34.29
RESET12: C110.2, JP88.10, R99.1, S13.3, S13.4, U37.29
RESET13: C119.2, JP95.10, R107.1, S14.3, S14.4, U40.29
RESET14: C128.2, JP102.10, R115.1, S15.3, S15.4, U43.29
RESET15: C137.2, JP109.10, R123.1, S16.3, S16.4, U46.29
RESET16: C146.2, JP116.10, R131.1, S17.3, S17.4, U49.29
RESET17: C155.2, JP123.10, R139.1, S18.3, S18.4, U52.29
RESET18: C164.2, JP130.10, R147.1, S19.3, S19.4, U55.29
RESET19: C173.2, JP137.10, R155.1, S20.3, S20.4, U58.29
RESET20: C182.2, JP144.10, R163.1, S21.3, S21.4, U61.29
RESET21: C191.2, JP151.10, R171.1, S22.3, S22.4, U64.29
RESET22: C200.2, JP158.10, R179.1, S23.3, S23.4, U67.29
RESET23: C209.2, JP165.10, R187.1, S24.3, S24.4, U70.29
RXI: JP2.11, JP8.4, R5.2, U2.30
RXI1: JP11.11, JP14.4, R13.2, U4.30
RXI2: JP18.11, JP21.4, R21.2, U7.30
RXI3: JP25.11, JP28.4, R29.2, U10.30
RXI4: JP32.11, JP35.4, R37.2, U13.30
RXI5: JP39.11, JP42.4, R45.2, U16.30
RXI6: JP46.11, JP49.4, R53.2, U19.30
RXI7: JP53.11, JP56.4, R61.2, U22.30
RXI8: JP60.11, JP63.4, R69.2, U25.30
RXI9: JP67.11, JP70.4, R77.2, U28.30
RXI10: JP74.11, JP77.4, R85.2, U31.30
RXI11: JP81.11, JP84.4, R93.2, U34.30
RXI12: JP88.11, JP91.4, R101.2, U37.30
RXI13: JP95.11, JP98.4, R109.2, U40.30
RXI14: JP102.11, JP105.4, R117.2, U43.30
RXI15: JP109.11, JP112.4, R125.2, U46.30
RXI16: JP116.11, JP119.4, R133.2, U49.30
RXI17: JP123.11, JP126.4, R141.2, U52.30
RXI18: JP130.11, JP133.4, R149.2, U55.30
RXI19: JP137.11, JP140.4, R157.2, U58.30
RXI20: JP144.11, JP147.4, R165.2, U61.30
RXI21: JP151.11, JP154.4, R173.2, U64.30
RXI22: JP158.11, JP161.4, R181.2, U67.30
RXI23: JP165.11, JP168.4, R189.2, U70.30
SCK: JP3.9, R4.2, U2.17
SCK1: JP10.9, R12.2, U4.17
SCK2: JP17.9, R20.2, U7.17
SCK3: JP24.9, R28.2, U10.17
SCK4: JP31.9, R36.2, U13.17
SCK5: JP38.9, R44.2, U16.17
SCK6: JP45.9, R52.2, U19.17
SCK7: JP52.9, R60.2, U22.17
SCK8: JP59.9, R68.2, U25.17
SCK9: JP66.9, R76.2, U28.17
SCK10: JP73.9, R84.2, U31.17
SCK11: JP80.9, R92.2, U34.17
SCK12: JP87.9, R100.2, U37.17
SCK13: JP94.9, R108.2, U40.17
SCK14: JP101.9, R116.2, U43.17
SCK15: JP108.9, R124.2, U46.17
SCK16: JP115.9, R132.2, U49.17
SCK17: JP122.9, R140.2, U52.17
SCK18: JP129.9, R148.2, U55.17
SCK19: JP136.9, R156.2, U58.17
SCK20: JP143.9, R164.2, U61.17
SCK21: JP150.9, R172.2, U64.17
SCK22: JP157.9, R180.2, U67.17
SCK23: JP164.9, R188.2, U70.17
TXO: JP2.12, JP8.3, R6.2, U2.31
TXO1: JP11.12, JP14.3, R14.2, U4.31
TXO2: JP18.12, JP21.3, R22.2, U7.31
TXO3: JP25.12, JP28.3, R30.2, U10.31
TXO4: JP32.12, JP35.3, R38.2, U13.31
TXO5: JP39.12, JP42.3, R46.2, U16.31
TXO6: JP46.12, JP49.3, R54.2, U19.31
TXO7: JP53.12, JP56.3, R62.2, U22.31
TXO8: JP60.12, JP63.3, R70.2, U25.31
TXO9: JP67.12, JP70.3, R78.2, U28.31
TXO10: JP74.12, JP77.3, R86.2, U31.31
TXO11: JP81.12, JP84.3, R94.2, U34.31
TXO12: JP88.12, JP91.3, R102.2, U37.31
TXO13: JP95.12, JP98.3, R110.2, U40.31
TXO14: JP102.12, JP105.3, R118.2, U43.31
TXO15: JP109.12, JP112.3, R126.2, U46.31
TXO16: JP116.12, JP119.3, R134.2, U49.31
TXO17: JP123.12, JP126.3, R142.2, U52.31
TXO18: JP130.12, JP133.3, R150.2, U55.31
TXO19: JP137.12, JP140.3, R158.2, U58.31
TXO20: JP144.12, JP147.3, R166.2, U61.31
TXO21: JP151.12, JP154.3, R174.2, U64.31
TXO22: JP158.12, JP161.3, R182.2, U67.31
TXO23: JP165.12, JP168.3, R190.2, U70.31
VBAT: JP6.2, JP7.2, Q1.3
VBAT1: JP12.2, JP13.2, Q3.3
VBAT2: JP19.2, JP20.2, Q5.3
VBAT3: JP26.2, JP27.2, Q7.3
VBAT4: JP33.2, JP34.2, Q9.3
VBAT5: JP40.2, JP41.2, Q11.3
VBAT6: JP47.2, JP48.2, Q13.3
VBAT7: JP54.2, JP55.2, Q15.3
VBAT8: JP61.2, JP62.2, Q17.3
VBAT9: JP68.2, JP69.2, Q19.3
VBAT10: JP75.2, JP76.2, Q21.3
VBAT11: JP82.2, JP83.2, Q23.3
VBAT12: JP89.2, JP90.2, Q25.3
VBAT13: JP96.2, JP97.2, Q27.3
VBAT14: JP103.2, JP104.2, Q29.3
VBAT15: JP110.2, JP111.2, Q31.3
VBAT16: JP117.2, JP118.2, Q33.3
VBAT17: JP124.2, JP125.2, Q35.3
VBAT18: JP131.2, JP132.2, Q37.3
VBAT19: JP138.2, JP139.2, Q39.3
VBAT20: JP145.2, JP146.2, Q41.3
VBAT21: JP152.2, JP153.2, Q43.3
VBAT22: JP159.2, JP160.2, Q45.3
VBAT23: JP166.2, JP167.2, Q47.3
VCC: C3.1, C6.1, C10.A, D4.C, JP3.1, JP8.1, R2.2, R3.2, R7.2, U2.4, U2.6, U2.18, U3.1, U3.2
VCC1: C1.1, C13.1, C17.A, D8.C, JP10.1, JP14.1, R10.2, R11.2, R15.2, U4.4, U4.6, U4.18, U5.1, U5.2
VCC2: C19.1, C22.1, C26.A, D12.C, JP17.1, JP21.1, R18.2, R19.2, R23.2, U7.4, U7.6, U7.18, U8.1, U8.2
VCC3: C28.1, C31.1, C35.A, D16.C, JP24.1, JP28.1, R26.2, R27.2, R31.2, U10.4, U10.6, U10.18, U11.1, U11.2
VCC4: C37.1, C40.1, C44.A, D20.C, JP31.1, JP35.1, R34.2, R35.2, R39.2, U13.4, U13.6, U13.18, U14.1, U14.2
VCC5: C46.1, C49.1, C53.A, D24.C, JP38.1, JP42.1, R42.2, R43.2, R47.2, U16.4, U16.6, U16.18, U17.1, U17.2
VCC6: C55.1, C58.1, C62.A, D28.C, JP45.1, JP49.1, R50.2, R51.2, R55.2, U19.4, U19.6, U19.18, U20.1, U20.2
VCC7: C64.1, C67.1, C71.A, D32.C, JP52.1, JP56.1, R58.2, R59.2, R63.2, U22.4, U22.6, U22.18, U23.1, U23.2
VCC8: C73.1, C76.1, C80.A, D36.C, JP59.1, JP63.1, R66.2, R67.2, R71.2, U25.4, U25.6, U25.18, U26.1, U26.2
VCC9: C82.1, C85.1, C89.A, D40.C, JP66.1, JP70.1, R74.2, R75.2, R79.2, U28.4, U28.6, U28.18, U29.1, U29.2
VCC10: C91.1, C94.1, C98.A, D44.C, JP73.1, JP77.1, R82.2, R83.2, R87.2, U31.4, U31.6, U31.18, U32.1, U32.2
VCC11: C100.1, C103.1, C107.A, D48.C, JP80.1, JP84.1, R90.2, R91.2, R95.2, U34.4, U34.6, U34.18, U35.1, U35.2
VCC12: C109.1, C112.1, C116.A, D52.C, JP87.1, JP91.1, R98.2, R99.2, R103.2, U37.4, U37.6, U37.18, U38.1, U38.2
VCC13: C118.1, C121.1, C125.A, D56.C, JP94.1, JP98.1, R106.2, R107.2, R111.2, U40.4, U40.6, U40.18, U41.1, U41.2
VCC14: C127.1, C130.1, C134.A, D60.C, JP101.1, JP105.1, R114.2, R115.2, R119.2, U43.4, U43.6, U43.18, U44.1, U44.2
VCC15: C136.1, C139.1, C143.A, D64.C, JP108.1, JP112.1, R122.2, R123.2, R127.2, U46.4, U46.6, U46.18, U47.1, U47.2
VCC16: C145.1, C148.1, C152.A, D68.C, JP115.1, JP119.1, R130.2, R131.2, R135.2, U49.4, U49.6, U49.18, U50.1, U50.2
VCC17: C154.1, C157.1, C161.A, D72.C, JP122.1, JP126.1, R138.2, R139.2, R143.2, U52.4, U52.6, U52.18, U53.1, U53.2
VCC18: C163.1, C166.1, C170.A, D76.C, JP129.1, JP133.1, R146.2, R147.2, R151.2, U55.4, U55.6, U55.18, U56.1, U56.2
VCC19: C172.1, C175.1, C179.A, D80.C, JP136.1, JP140.1, R154.2, R155.2, R159.2, U58.4, U58.6, U58.18, U59.1, U59.2
VCC20: C181.1, C184.1, C188.A, D84.C, JP143.1, JP147.1, R162.2, R163.2, R167.2, U61.4, U61.6, U61.18, U62.1, U62.2
VCC21: C190.1, C193.1, C197.A, D88.C, JP150.1, JP154.1, R170.2, R171.2, R175.2, U64.4, U64.6, U64.18, U65.1, U65.2
VCC22: C199.1, C202.1, C206.A, D92.C, JP157.1, JP161.1, R178.2, R179.2, R183.2, U67.4, U67.6, U67.18, U68.1, U68.2
VCC23: C208.1, C211.1, C215.A, D96.C, JP164.1, JP168.1, R186.2, R187.2, R191.2, U70.4, U70.6, U70.18, U71.1, U71.2
VCC_1: C9.A, D1.C, L1.P$1, Q1.2
VCC_2: C16.A, D5.C, L2.P$1, Q3.2
VCC_3: C25.A, D9.C, L3.P$1, Q5.2
VCC_4: C34.A, D13.C, L4.P$1, Q7.2
VCC_5: C43.A, D17.C, L5.P$1, Q9.2
VCC_6: C52.A, D21.C, L6.P$1, Q11.2
VCC_7: C61.A, D25.C, L7.P$1, Q13.2
VCC_8: C70.A, D29.C, L8.P$1, Q15.2
VCC_9: C79.A, D33.C, L9.P$1, Q17.2
VCC_10: C88.A, D37.C, L10.P$1, Q19.2
VCC_11: C97.A, D41.C, L11.P$1, Q21.2
VCC_12: C106.A, D45.C, L12.P$1, Q23.2
VCC_13: C115.A, D49.C, L13.P$1, Q25.2
VCC_14: C124.A, D53.C, L14.P$1, Q27.2
VCC_15: C133.A, D57.C, L15.P$1, Q29.2
VCC_16: C142.A, D61.C, L16.P$1, Q31.2
VCC_17: C151.A, D65.C, L17.P$1, Q33.2
VCC_18: C160.A, D69.C, L18.P$1, Q35.2
VCC_19: C169.A, D73.C, L19.P$1, Q37.2
VCC_20: C178.A, D77.C, L20.P$1, Q39.2
VCC_21: C187.A, D81.C, L21.P$1, Q41.2
VCC_22: C196.A, D85.C, L22.P$1, Q43.2
VCC_23: C205.A, D89.C, L23.P$1, Q45.2
VCC_24: C214.A, D93.C, L24.P$1, Q47.2
V_USB: C7.1, C8.1, D1.A, JP1.5V, Q1.1, R1.2, U1.15
V_USB1: C14.1, C15.1, D5.A, JP4.5V, Q3.1, R9.2, U6.15
V_USB2: C23.1, C24.1, D9.A, JP15.5V, Q5.1, R17.2, U9.15
V_USB3: C32.1, C33.1, D13.A, JP22.5V, Q7.1, R25.2, U12.15
V_USB4: C41.1, C42.1, D17.A, JP29.5V, Q9.1, R33.2, U15.15
V_USB5: C50.1, C51.1, D21.A, JP36.5V, Q11.1, R41.2, U18.15
V_USB6: C59.1, C60.1, D25.A, JP43.5V, Q13.1, R49.2, U21.15
V_USB7: C68.1, C69.1, D29.A, JP50.5V, Q15.1, R57.2, U24.15
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
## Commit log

2015-10-03 getting close to review
2015-10-03 ready for peer review
2015-10-06 New FTDI and serial pinout
2015-10-06 ready for review
2015-10-06 cleanup
2015-10-06 fixed errors
2015-10-07 Approved DRCs
2015-10-07 proto panel created and cammed
2015-10-07 zipped 'em
2015-10-07 added "route out" removed gerbers
2015-10-07 Adding back linked .sch/.brd files
2015-12-02 Completed electrical testing
2015-12-02 Hardware changes for reds review
2015-12-07 Docu and design touch up
2015-12-10 Getting ready for reds
2015-12-14 Re-approved DRC, renamed U4
2015-12-21 created panel v10
2016-01-28 Updating README with proper links
2016-01-29 release
2016-01-29 Resolved conflict
2016-01-29 Finished readme
2016-01-29 fixed typo
2016-01-29 Fixed tag link
2016-03-07 Fixing README descriptions
2020-05-29 Update README
    Adding retired note for archived tutorial.
